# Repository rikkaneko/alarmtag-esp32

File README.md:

# alarmtag-esp32
An alarm tag using ESP32.

## Supported feature
+ Pin authentication
+ Toggle alarm buzzer remotely
+ Customize device policies

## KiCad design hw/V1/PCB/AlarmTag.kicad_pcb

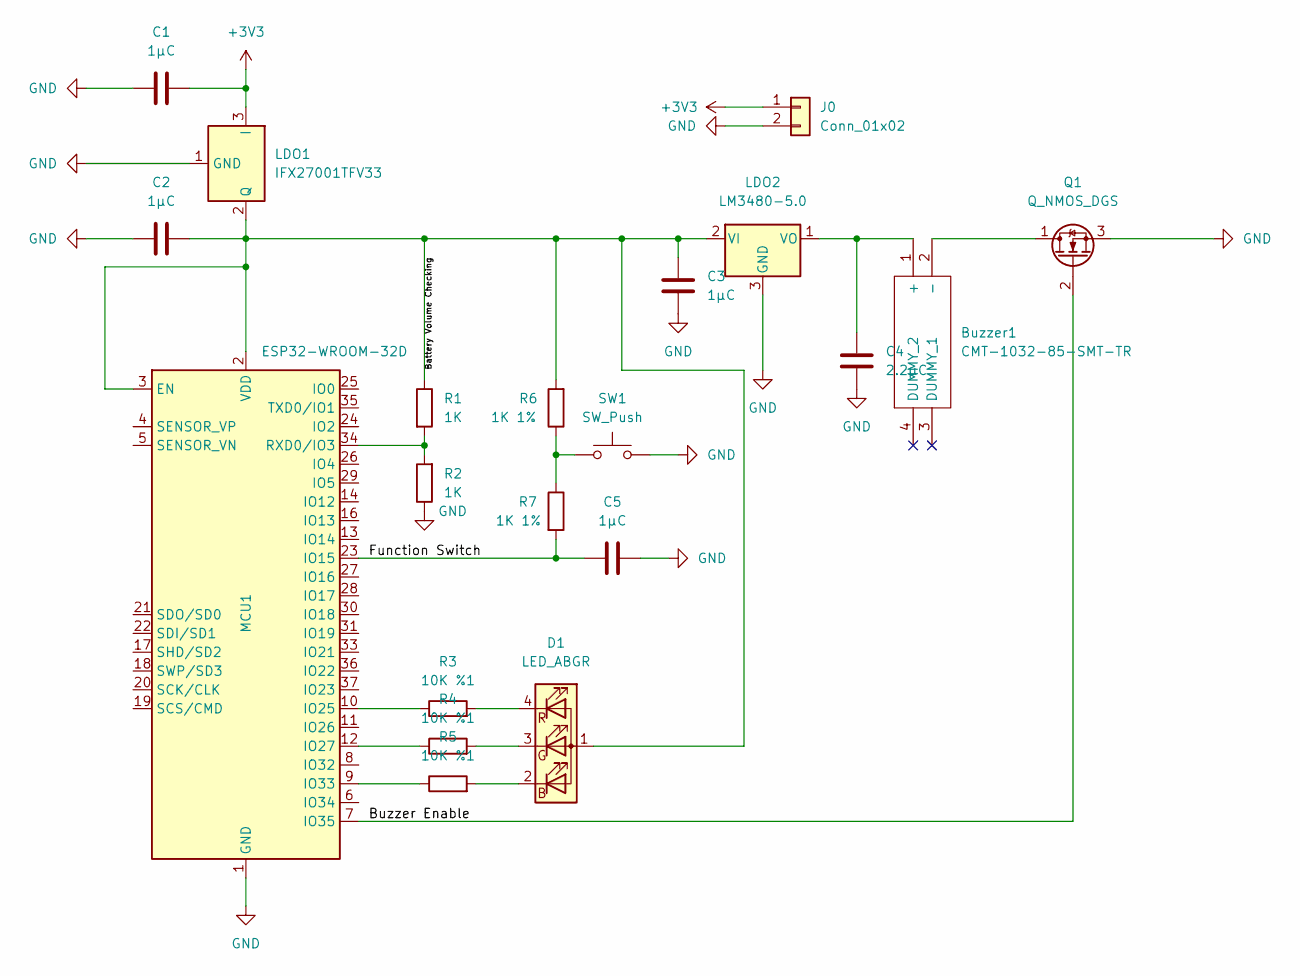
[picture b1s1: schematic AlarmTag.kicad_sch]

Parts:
Buzzer1: CMT-1032-85-SMT-TR; CMT103285SMTTR; Manufacturer_Part_Number CMT-1032-85-SMT-TR; Mouser Part Number 490-CMT-1032-85SMTTR
C1, C2, C3, C5: 1μC; C_0603_1608Metric
C4: 2.2μC; C_0603_1608Metric
D1: LED_ABGR; LED_RGB_Wuerth-PLCC4_3.2x2.8mm_150141M173100
J0: Conn_01x02; PinHeader_1x02_P1.00mm_Horizontal
LDO1: IFX27001TFV33; TO-252-3_TabPin2
LDO2: LM3480-5.0; SOT-23
MCU1: ESP32-WROOM-32D; ESP32-WROOM-32
Q1: Q_NMOS_DGS; SOT-23
R1, R2: 1K; R_0603_1608Metric
R3, R4, R5: 10K %1; R_0603_1608Metric
R6, R7: 1K 1%; R_0603_1608Metric
SW1: SW_Push; SW_PUSH_6mm

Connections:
+3V3: C1.2, J0.1, LDO1.3 (I)
/Buzzer Enable: MCU1.7 (IO35), Q1.2 (G)
/Function Switch: C5.2, MCU1.23 (IO15), R7.2
GND: C1.1, C2.1, C3.2, C4.2, C5.1, J0.2, LDO1.1 (GND), LDO2.3 (GND), MCU1.1 (GND), MCU1.15 (GND), MCU1.38 (GND), MCU1.39 (GND), Q1.3 (S), R2.1, SW1.2
unnamed: Buzzer1.1 (+), C4.1, LDO2.1 (VO)
unnamed: Buzzer1.2 (-), Q1.1 (D)
unnamed: C2.2, C3.1, D1.1 (A), LDO1.2 (Q), LDO2.2 (VI), MCU1.2 (VDD), MCU1.3 (EN), R1.1, R6.2
unnamed: D1.2 (BK), R5.2
unnamed: D1.3 (GK), R4.2
unnamed: D1.4 (RK), R3.2
unnamed: MCU1.9 (IO33), R5.1
unnamed: MCU1.10 (IO25), R3.1
unnamed: MCU1.12 (IO27), R4.1
unnamed: MCU1.34 (RXD0/IO3), R1.2, R2.2
unnamed: R6.1, R7.1, SW1.1

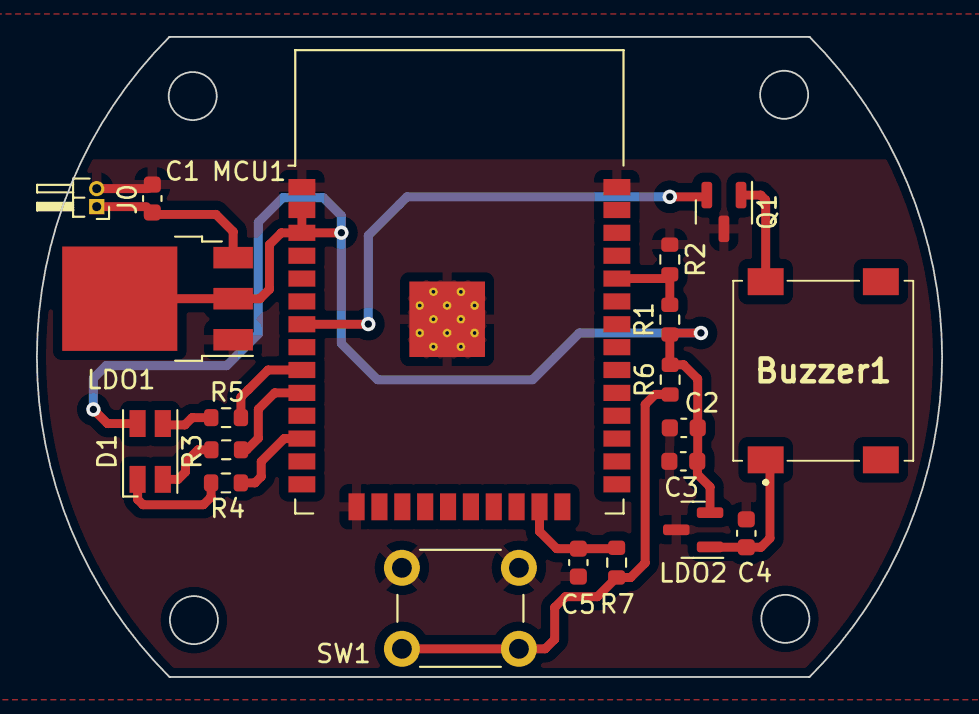
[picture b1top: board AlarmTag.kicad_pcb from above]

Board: 2 copper layers, 50.3 x 35.6 mm, 20 parts (0 on the bottom side), 15 nets.

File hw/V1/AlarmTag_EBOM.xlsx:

Comment | Designator | Footprint | 嘉立创元件编号 | 生产商编号
1uC | C1, C2, C3, C5 | 0603_C | C1592 | CL10A105KO8NNNC
2.2uC | C4 | 0603_C | C23630 | CL10A225KO8NNNC
LED_ABGR | D1 | PLCC-4 | 海外 | 150141M173100
IFX27001TFV33 | LDO1 | TO-252-3 | C536024 | IFX27001TFV33
LM3480IM3X-5.0 | LDO2 | SOT-23 | C129960 | LM3480IM3X-5.0
CMT-1032-85-SMT-TR | LS1 | CMT-1032-85-SMT-TR | 海外 | CMT-1032-85-SMT-TR
ESP32-WROOM-32UE | MCU1 | SOIC-8_150mil | C701341 | ESP32-WROOM-32UE
Q_NMOS_DGS | Q1 | SOT-23 | C8545 | 2N7002
10K %1 | R1, R2, R3, R4, R5 | 0603_R | C25804 | 0603WAF1002T5E
1K 1% | R6, R7 | 0603_R | C21190 | 0603WAF1001T5E
SW_Push | SW1 | 4P,6x6mm | C93157 | B3F-1000

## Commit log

2023-02-01 Add README
2023-02-10 Update RGB LED and buzzer pinout
2023-03-07 add hw V1
2023-03-07 update hardware V1
